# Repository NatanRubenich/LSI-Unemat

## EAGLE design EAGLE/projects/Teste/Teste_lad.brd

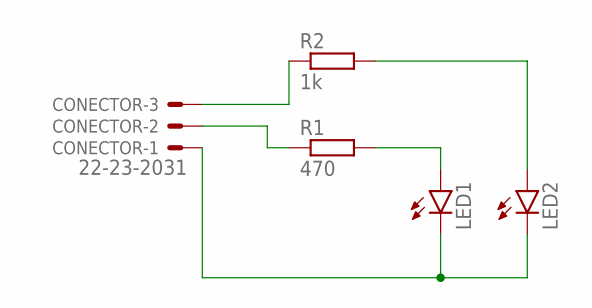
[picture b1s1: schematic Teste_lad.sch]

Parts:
CONECTOR: 22-23-2031
LED1, LED2: LED5MM
R1: 470; 0204/7
R2: 1k; 0204/7

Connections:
unnamed: CONECTOR.3, R2.1
unnamed: CONECTOR.2, R1.1
unnamed: LED2.A, R2.2
unnamed: LED1.A, R1.2
unnamed: CONECTOR.1, LED1.K (C), LED2.K (C)

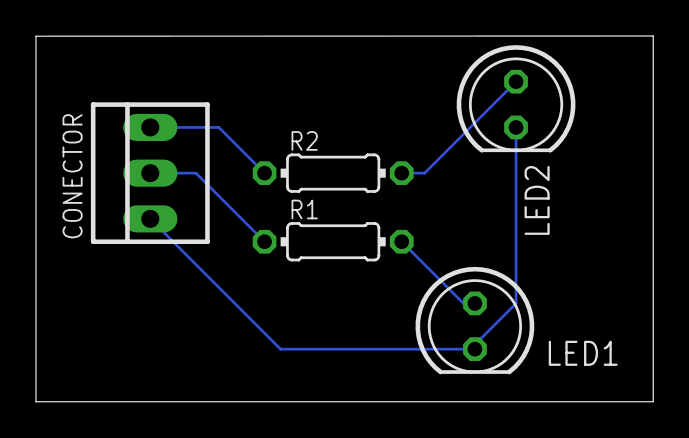
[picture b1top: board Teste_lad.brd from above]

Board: 2 copper layers, 34.3 x 20.3 mm, 5 parts (0 on the bottom side), 5 nets.

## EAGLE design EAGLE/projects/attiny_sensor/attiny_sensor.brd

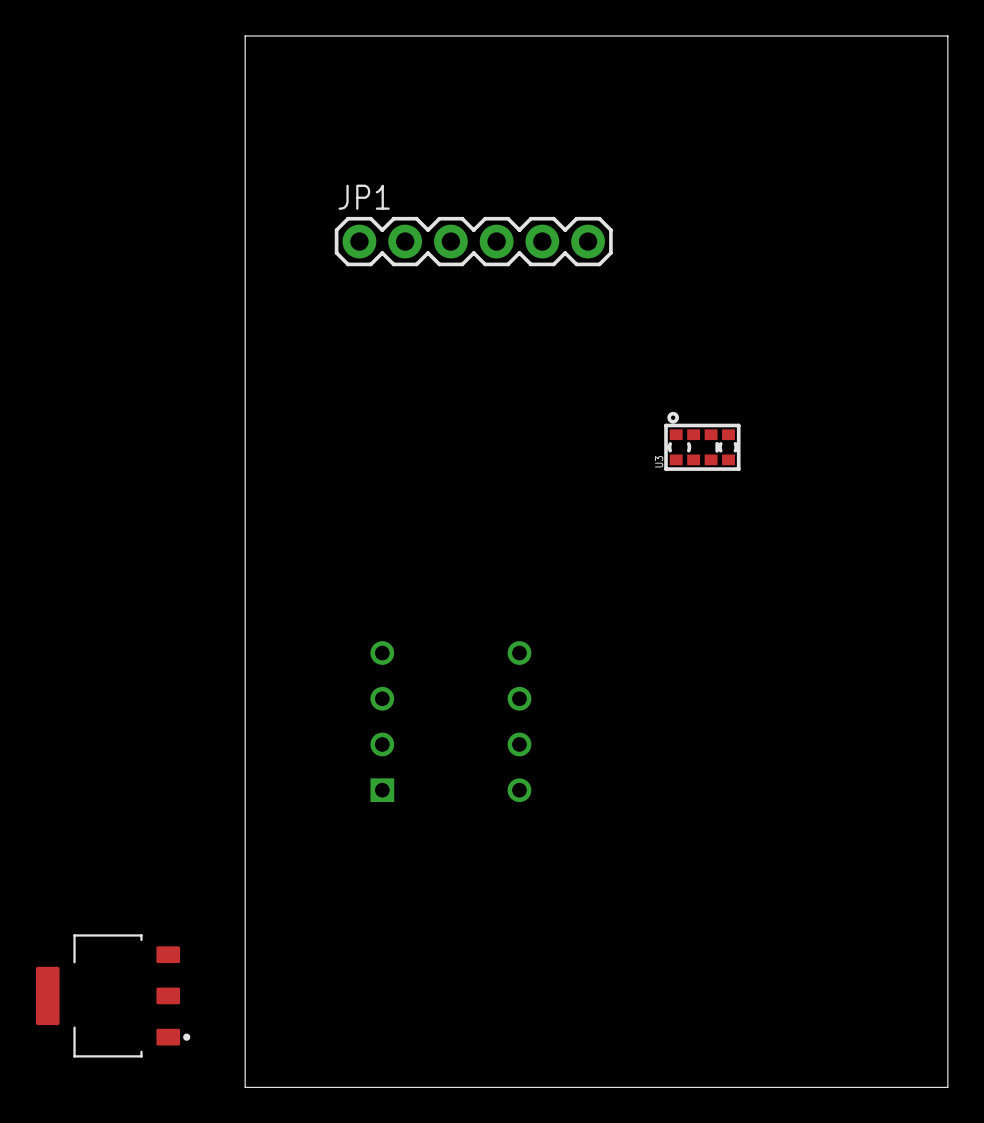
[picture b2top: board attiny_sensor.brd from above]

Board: 2 copper layers, 39.0 x 58.4 mm, 4 parts (1 on the bottom side), 5 nets, no tracks yet.

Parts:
JP1: 1X06
U1: ATTINY85-20PU; DIP762W46P254L927H533Q8B
U2: AMS1117-3.3; SOT229P700X180-4N
U3: APDS-9960

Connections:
unnamed: U1.7, U3.7
unnamed: U1.2, U3.1
unnamed: U1.5, U3.2
unnamed: U3.3, U3.4
unnamed: U1.4, U3.6

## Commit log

2021-02-02 Criado o arquivo main do sensor
    Criado o arquivo main do sensor
2021-02-02 Up Adafruit
2021-02-03 Gestos de ligar e desligar
    Foi implementado gestos de ligar(cima) desligar(baixo)
2021-02-04 Gestos laterais para controle de intencidade
    Adicionei gestos laterais para controle de intensidade sendo de 0 (desligado) a 4 (totalemente ligado). Tirei os ponteiros e deixei tudo dentro da função usando uma variavel static.
2021-02-23 Bene
2021-04-15 Eagle projects and libraries

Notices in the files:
parts and their libraries:
SparkFun-Connectors: Licensing: Creative Commons ShareAlike 4.0 International - https://creativecommons.org/licenses/by-sa/4.0
